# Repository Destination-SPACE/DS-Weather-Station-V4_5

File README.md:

<div align="center">
    
    <h1>Destination Weather Station v4.5.2</h1>
    <p>An Open Source Remote Sensing Platform for National Taiwan Normal University 🇹🇼</p>
</div>

## 🌟 About the Project
Destination Weather Station is the the latest version of remote sensing tools developed to teach students across Taiwan about climate science and remote sensing in partnership with National Taiwan Normal University.
## ⚙️ Hardware
All hardware files can be found [here](hardware/destinationWeatherStation_v4-5/)
## 💻 Software
All program files can be found [here](software)
## 🗂️ Documentation
Documentation for the weather station can be found [here](https://destination-space.github.io/DS-Weather-Station-V4_5/)
## Licenses
Each of the above sections are individually licensed. Terms and conditions apply within their respective folders.

**Documentation - [Apache License 2.0](docs/LICENSE)** <br>
**Hardware - [CERN-OHL-P](hardware/destinationWeatherStation_v4-5//LICENSE)** <br>
**Software - [The MIT License](software/LICENSE)**

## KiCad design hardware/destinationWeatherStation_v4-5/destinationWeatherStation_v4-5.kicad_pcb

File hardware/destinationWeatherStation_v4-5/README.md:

# Destination Weather Station v4.5 Hardware
KiCad files for Destination Weather Station v4.5

## KiCanvas
View schematic and PCB files with [KiCanvas](https://kicanvas.org/?github=https%3A%2F%2Fgithub.com%2FDestination-SPACE%2FDS-Weather-Station-V4_5%2Ftree%2Fmain%2Fhardware%2FdestinationWeatherStation_v4-5)

## Directory
### [🧾 Bill of Materials](bom/bom.md)
### [📐 Gerbers](manufacturing/gerbers)
### [📰 Schematics](manufacturing/destinationWeatherStation_v4-5.pdf)

Licensed under [CERN-OHL-P](LICENSE)

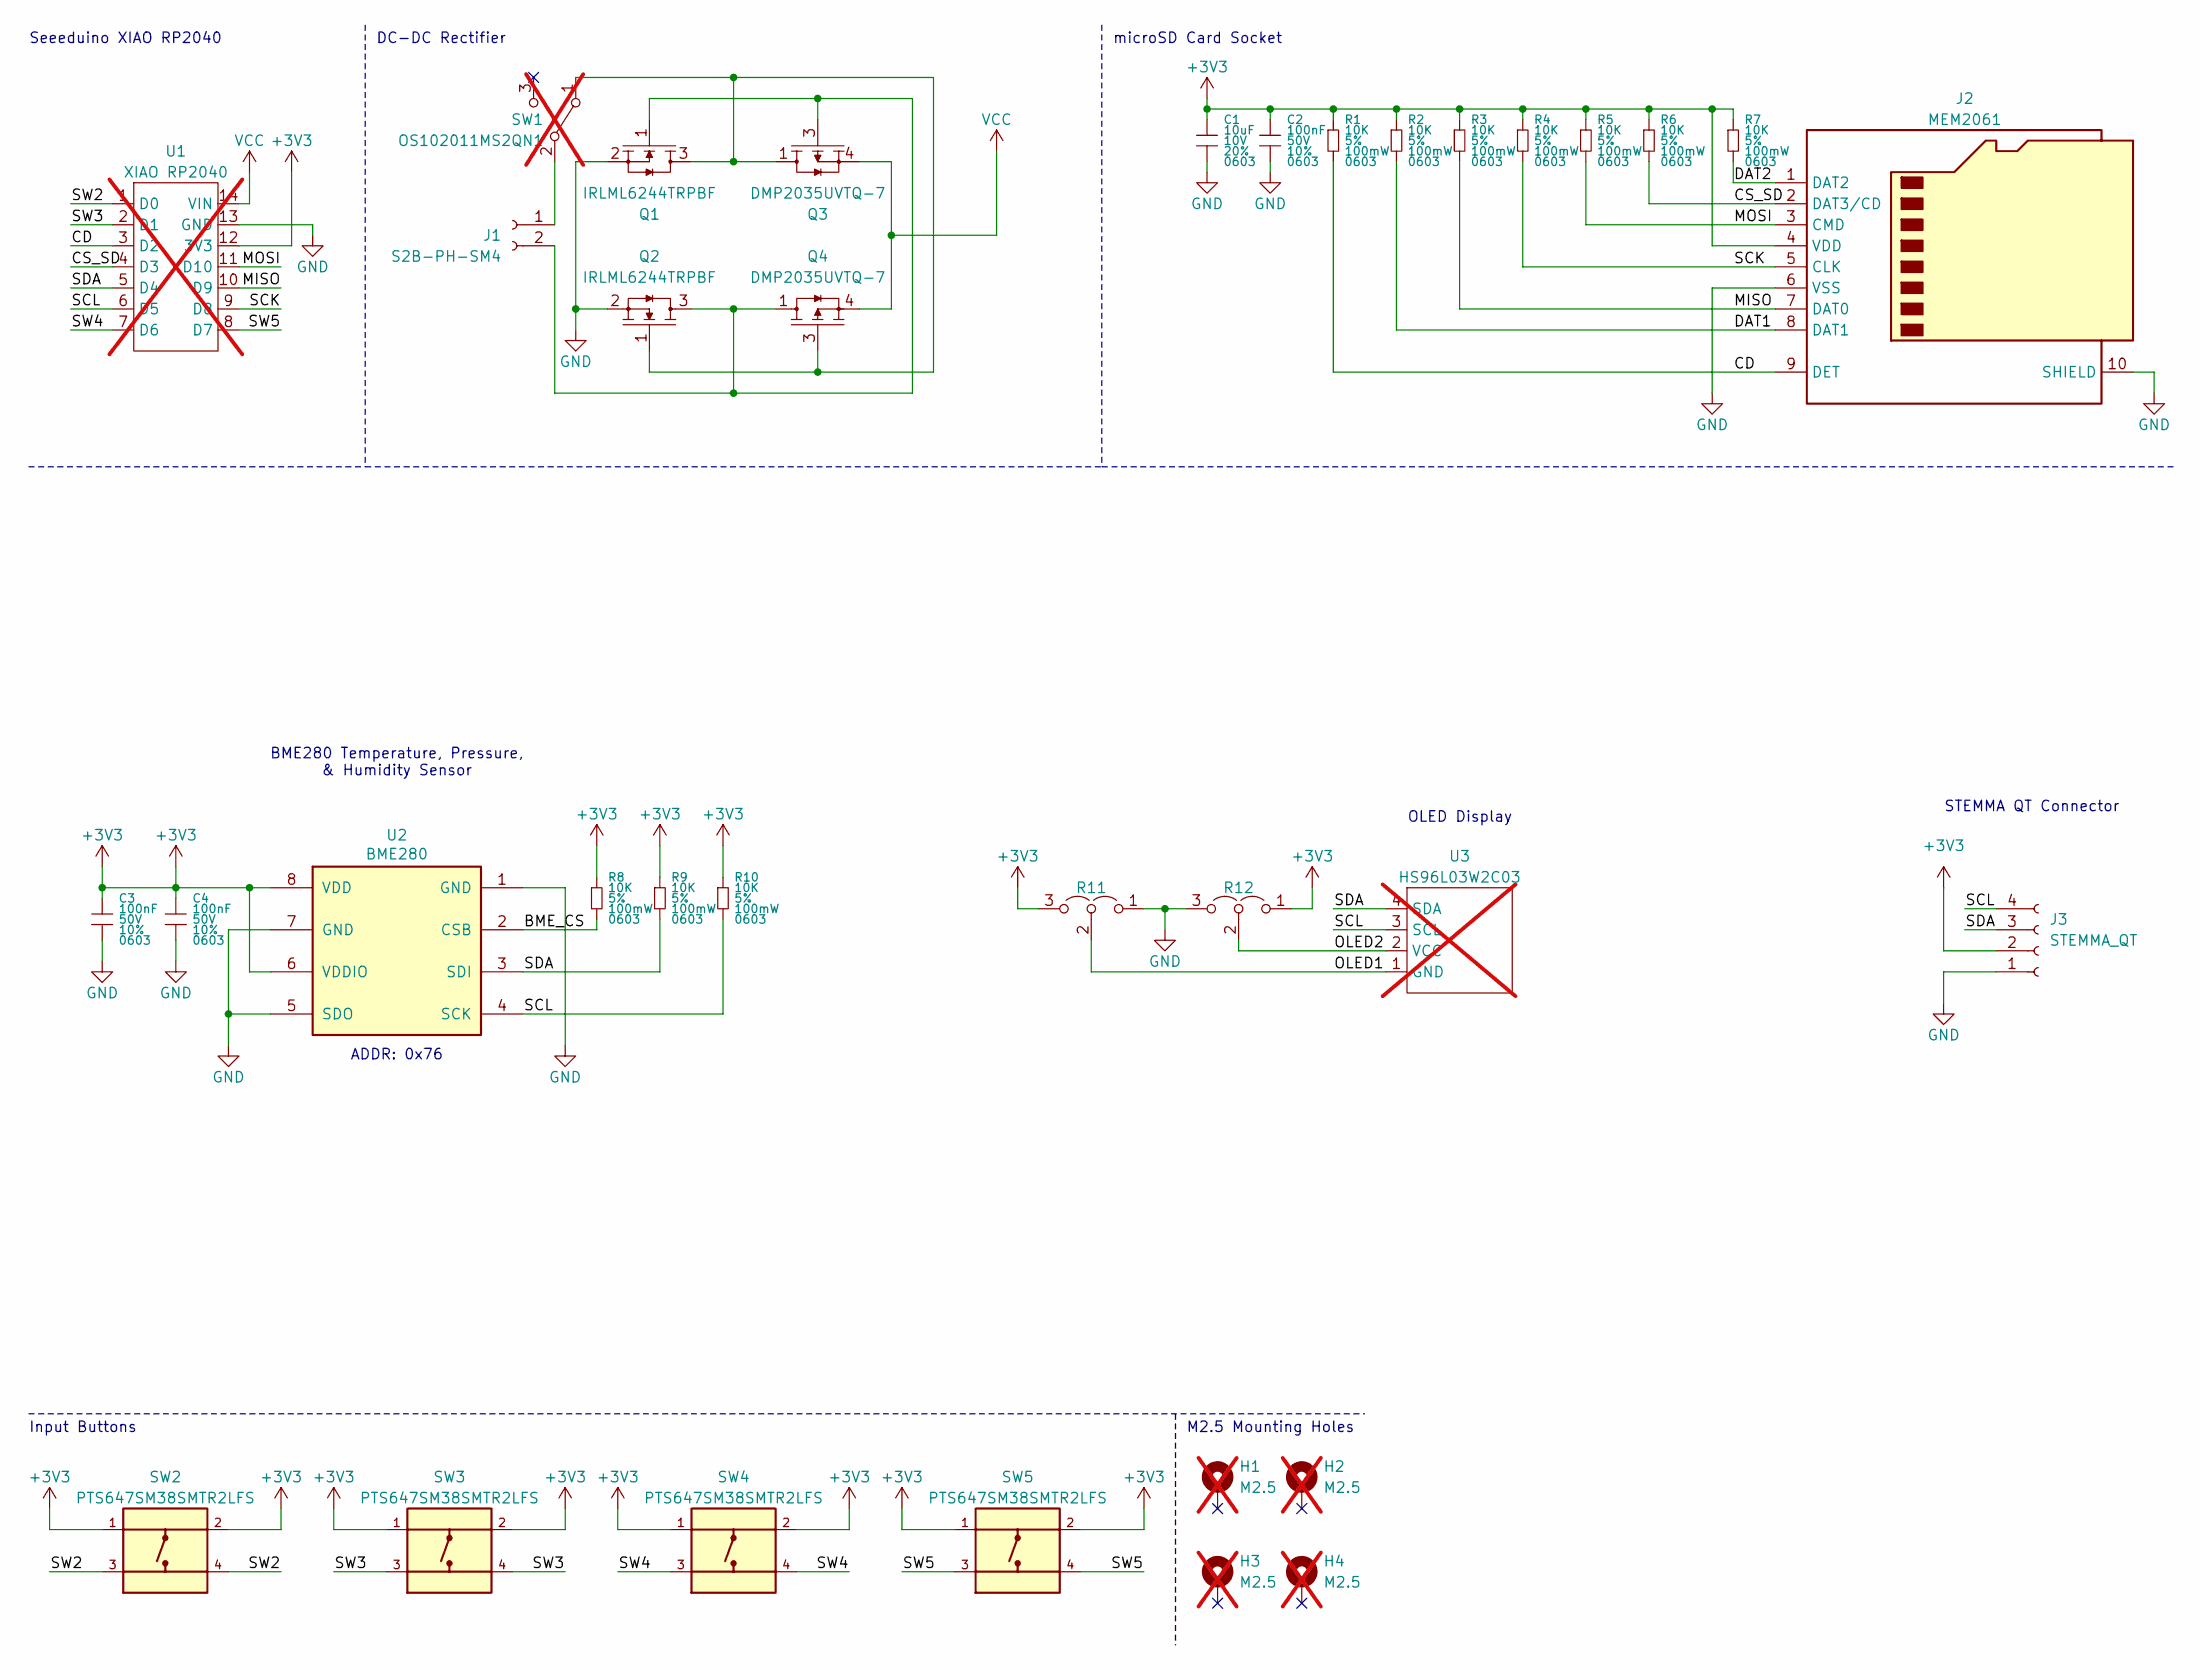
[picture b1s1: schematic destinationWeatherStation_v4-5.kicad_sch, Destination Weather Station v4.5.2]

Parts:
C1: 10uF; CAPC160X80X88L35N; Tolerance 20%; Voltage Rating 10V; MPN KGM15CR51A106MT; JLCPCB PN C1691
C2, C3, C4: 100nF; CAPC160X80X88L35N; Tolerance 10%; Voltage Rating 50V; MPN KGM15AR51H104KT; JLCPCB PN C1590
H1, H2, H3, H4: M2.5; M2.54_NPTH; not fitted
J1: S2B-PH-SM4; JST-PH-S2B-SM4-TB; MPN S2B-PH-SM4-TB(LF)(SN); JLCPCB PN C295747
J2: MEM2061; MPN MEM2061-01-188-00-A; JLCPCB PN C5151738
J3: STEMMA_QT; JST_SH_SM04B-SRSS-TB; MPN SM04B-SRSS-TB; JLCPCB PN C160404
Q1, Q2: IRLML6244TRPBF; MPN IRLML6244TRPBF; JLCPCB PN C5123965
Q3, Q4: DMP2035UVTQ-7; SOT23-6P95_280X100L40X37N; MPN DMP2035UVTQ-7; JLCPCB PN C5126680
R1, R2, R3, R4, R5, R6, R7, R8, R9, R10: 10K; RESC160X80X55L30N; Tolerance 5%; Power Rating 100mW; MPN CRCW060310K0JNEB; JLCPCB PN C1511834
R11, R12: 0R; ResistorJumper-3; MPN CRCW06030000Z0EA; JLCPCB PN C844915
SW1: OS102011MS2QN1; MPN OS102011MS2QN1; JLCPCB PN C221829; not fitted
SW2, SW3, SW4, SW5: PTS647SM38SMTR2LFS; SW_4.5x4.5; MPN PTS 647 SM38 SMTR2 LFS; JLCPCB PN C2689502
U1: XIAO RP2040; QtPy; MPN RP2040; JLCPCB PN N/A; not fitted
U2: BME280; MPN BME280; JLCPCB PN C92489
U3: HS96L03W2C03; MPN HS96L03W2C03; JLCPCB PN C5248080; not fitted

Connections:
+3V3: C1.1, C2.1, C3.1, C4.1, J2.4 (VDD), J3.2, R1.1, R2.1, R3.1, R4.1, R5.1, R6.1, R7.1, R8.1, R9.1, R10.1, R11.3 (B), R12.1 (A), SW2.1, SW2.2, SW3.1, SW3.2, SW4.1, SW4.2, SW5.1, SW5.2, U1.12 (3V3), U2.6 (VDDIO), U2.8 (VDD)
/BME_CS: R8.2, U2.2 (CSB)
/CD: J2.9 (DET), R1.2, U1.3 (D2)
/CS_SD: J2.2 (DAT3/CD), R6.2, U1.4 (D3)
/DAT1: J2.8 (DAT1), R2.2
/DAT2: J2.1 (DAT2), R7.2
/MISO: J2.7 (DAT0), R3.2, U1.10 (D9)
/MOSI: J2.3 (CMD), R5.2, U1.11 (D10)
/OLED1: R11.2 (C), U3.1 (GND)
/OLED2: R12.2 (C), U3.2 (VCC)
/SCK: J2.5 (CLK), R4.2, U1.9 (D8)
/SCL: J3.4, R10.2, U1.6 (D5), U2.4 (SCK), U3.3 (SCL)
/SDA: J3.3, R9.2, U1.5 (D4), U2.3 (SDI), U3.4 (SDA)
/SW2: SW2.3, SW2.4, U1.1 (D0)
/SW3: SW3.3, SW3.4, U1.2 (D1)
/SW4: SW4.3, SW4.4, U1.7 (D6)
/SW5: SW5.3, SW5.4, U1.8 (D7)
GND: C1.2, C2.2, C3.2, C4.2, J2.6 (VSS), J2.10 (SHIELD), J3.1, Q1.2, Q2.2, R11.1 (A), R12.3 (B), U1.13 (GND), U2.1 (GND), U2.5 (SDO), U2.7 (GND)
unnamed: J1.1, SW1.2 (B)
unnamed: J1.2, Q1.1, Q2.3, Q3.3, Q4.1, Q4.2, Q4.5, Q4.6
unnamed: Q1.3, Q2.1, Q3.1, Q3.2, Q3.5, Q3.6, Q4.3, SW1.1 (A)
VCC: Q3.4, Q4.4, U1.14 (VIN)

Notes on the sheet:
DC-DC Rectifier
ADDR: 0x76
OLED Display
Seeeduino XIAO RP2040
M2.5 Mounting Holes
Input Buttons
microSD Card Socket
STEMMA QT Connector
BME280 Temperature, Pressure, & Humidity Sensor

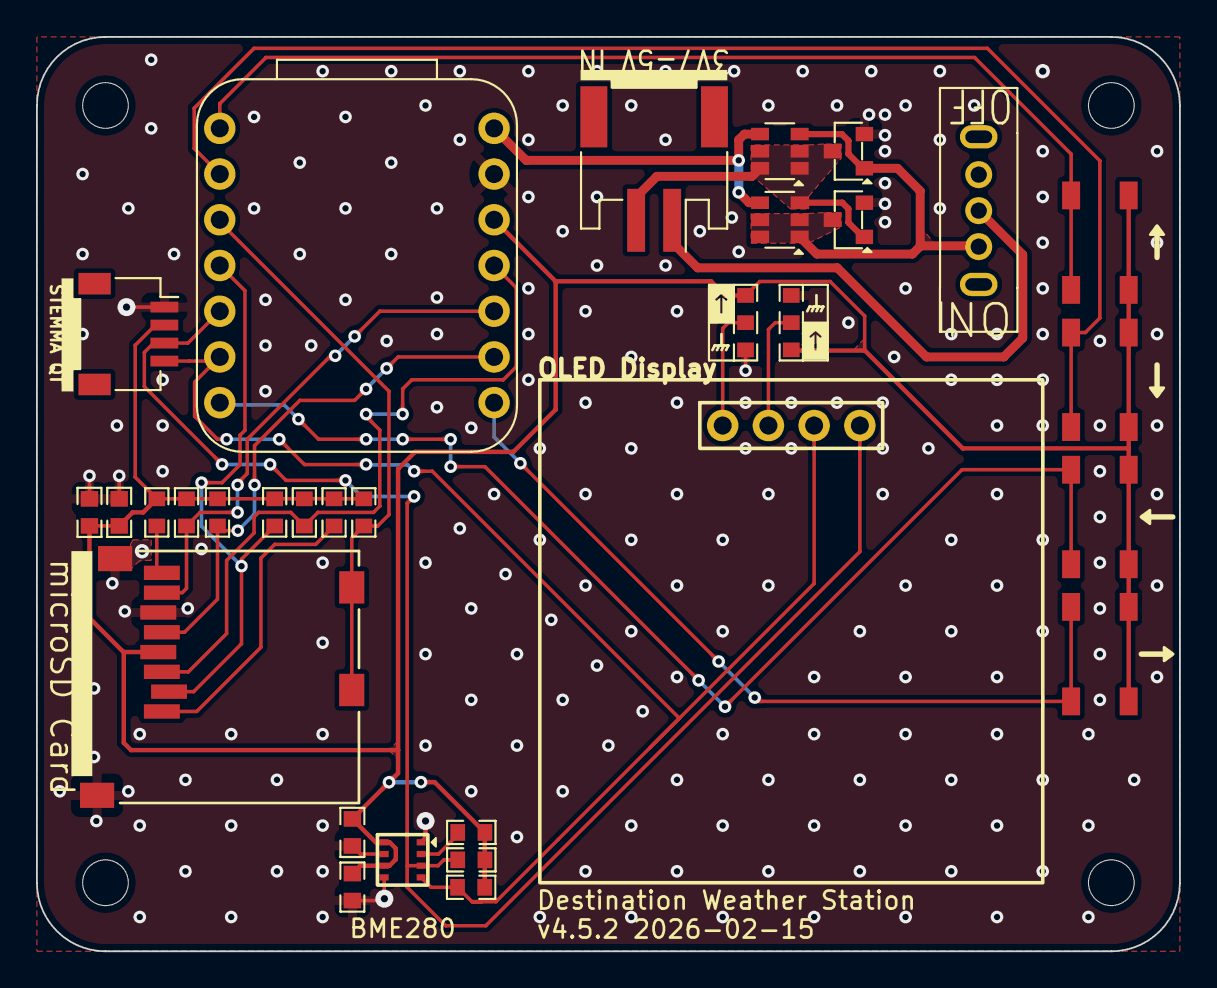
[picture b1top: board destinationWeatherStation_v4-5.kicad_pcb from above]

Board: 2 copper layers, 63.5 x 50.8 mm, 35 parts (0 on the bottom side), 22 nets.

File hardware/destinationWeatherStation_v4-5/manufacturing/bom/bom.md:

# Bill of Materials
*Note: Some parts may be replaced with suitable alternatives

| Item | Qty | Reference | Value | Datasheet | Manufacturer | Manufacturer Part Number | Package |
|-----:|----:|:---------:|:-----:|:----------|:-------------|:-------------------------|--------:|
| 1 | 1 | C1 | 10uF | [AVX-CX5R-KGM](../datasheets/AVX-CX5R-KGM-MLCC.pdf) | KYOCERA AVX | KGM15CR51A106MT | 0603 |
| 2 | 3 | C2, C3, C4 | 0.1uF | [AVX-CX5R-KGM](../datasheets/AVX-CX5R-KGM-MLCC.pdf) | KYOCERA AVX | KGM15AR51H104KT | 0603 | 
| 3 | 10 | R1, R2, R3, R4, R5, R6, R7, R8, R9, R10 | 10K | [D/CRCW e3](../datasheets/Vishay-Dale-DCRCWe3.pdf) | Vishay Dale | CRCW060310K0JNEB | 0603 |
| 3 | 2 | R11, R12 | 0R | [D/CRCW e3](../datasheets/Vishay-Dale-DCRCWe3.pdf) | Vishay Dale | CRCW06030000Z0EA | 0603 |
| 4 | 2 | Q1, Q2 | IRLML6244TRPBF | [IRLML6244TRPBF](../datasheets//Infineon-IRLML6244.pdf) | Infineon Technologies | IRLML6244TRPBF | SOT-23 |
| 5 | 2 | Q3, Q4 | DMP2035UVTQ | [DMP2035UVTQ](../datasheets/Diodes-Incorporated-DMP2035UVTQ.pdf) | Diodes Incorporated | DMP2035UVTQ-7 | TSOT26 |
| 6 | 1 | U1 | XIAO RP2040 | [XIAO RP2040](https://wiki.seeedstudio.com/XIAO-RP2040/) | Seeed Studio | XIAO RP2040 | N/A |
| 7 | 1 | U2 | BME280 | [BME280](../datasheets/BST-BME280.pdf) | Bosch Sensortec | BME280 | 2.5x2.5mm LGA |
| 8 | 1 | U3 | OLED | [HS96L03W2C03](../datasheets/HS-HS96L03W2C03.pdf) | SHENZHEN HANSHENG INDUSTRAIL CO. | HS96L03W2C03 | N/A |
| 9 | 1 | SW1 | OS102011MS2QN1 | [OS102011MS2QN1](https://www.ckswitches.com/media/1428/os.pdf) | C&K | OS102011MS2QN1 | N/A |
| 10 | 4 | SW2, SW3, SW4, SW5 | PTS647SM38SMTR2LFS | [PTS647SM38SMTR2LFS](../datasheets/C&K-PTS647.pdf) | C&K | PTS 647 SM38 SMTR2 LFS | N/A |
| 11 | 1 | J1 | S2B-PH-SM4 | [JST-PH](../datasheets/JST-PH-Connectors.pdf) | JST Sales America Inc. | S2B-PH-SM4-TB(LF)(SN) | N/A |
| 12 | 1 | J2 | MEM2061 | [MEM2061](../datasheets//GCT-MEM2061.pdf) | GCT | MEM2061-01-188-00-A | N/A |
| 13 | 1 | J3 | SM04B-SRSS | [JST-SH](../datasheets/JST-SH-Connectors.pdf) | JST Sales America Inc. | SM04B-SRSS-TB | N/A |

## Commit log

2026-01-30 fixing for final version
2026-02-02 removed local copy of datasheets
2026-02-02 fixed symbols, footprints, and models
2026-02-02 exported new gerbers
2026-02-02 exported gerbers
2026-02-02 fixed schematic and linked datasheets
2026-02-02 nudged traces and relinked footprints and models
2026-02-10 moved gerbers
2026-02-10 moved BOM
2026-02-10 manufacturing files
2026-02-10 fixed footprints
2026-02-10 fixed symbols
2026-02-10 exported schematic
2026-02-10 pages stuff
2026-02-10 removed old files
2026-02-10 updated dates and links
2026-02-10 removed workspace
2026-02-10 updated docs link
2026-02-15 re-exported gerbers
2026-02-15 moved JLCPCB manufacturing files to subfolder
2026-02-15 updated silkscreen and fixed copper pours
2026-02-15 removed files
2026-02-15 fixed dimension
2026-02-15 added manufacturing instructions
2026-02-15 fixed links
2026-02-15 fixed formatting
2026-02-15 formatting
2026-02-16 moved file
2026-02-16 added doc pages for manufacturing and ordering kits
2026-02-16 added manufacturing docs to index
2026-02-16 fixed link formatting
2026-02-16 fixed table formatting
2026-02-16 spelling
2026-02-16 added compile option for PDF docs
2026-02-16 fixed rst formatting and added stuff to fix code block compilation
2026-02-16 fixed paths
2026-02-16 fixed links formatting
2026-02-16 title block formatting
2026-02-16 fixed name
2026-02-16 deploy: 50295bd5e307e5668bf9fccd20f9833d0fbd5230
2026-02-16 fixed workflow to build pdf
2026-02-16 changed name of workflow
2026-02-16 fixed pdf workflow?
2026-02-16 fixed equation formatting
2026-02-16 removed lines
2026-02-16 removed
2026-02-16 fixed R11 and R12 placement
2026-02-16 fixed resistor placement
2026-02-16 added jlcpcb images
2026-02-16 added JLCPCB image
2026-02-16 fixed images path
2026-02-16 exported schematics
2026-02-16 exported docs pdf
